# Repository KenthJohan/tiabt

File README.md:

# tiabt
Low cost 8 channels transimpedance amplifier with bluetooth.

## circuit1
The `/circuit1` is low cost.
* op-amp `MCP6004` 0.5 EUR<br>

|Name                  |Category|  EUR|Footprint |   |   |   |   |   |   |
|----------------------|--------|-----|----------|---|---|---|---|---|---|
| [MCP6004][3]         | Op-Amp |0.5  |SOIC-14   |   |   |   |   |   |   |
| [MCP3564][4]         | ADC    |6    |          |   |   |   |   |   |   |
| [nRF52840 Dongle][1] | MCU    |     |          |   |   |   |   |   |   |
|                      |        |     |          |   |   |   |   |   |   |
|                      |        |     |          |   |   |   |   |   |   |
|                      |        |     |          |   |   |   |   |   |   |
|                      |        |     |          |   |   |   |   |   |   |
|                      |        |     |          |   |   |   |   |   |   |
|                      |        |     |          |   |   |   |   |   |   |
|                      |        |     |          |   |   |   |   |   |   |

## circuit2
The `/circuit2` is high cost.

|Name                  |Category|  EUR|Footprint|   |   |   |   |   |   |
|----------------------|--------|-----|---------|---|---|---|---|---|---|
| [MCP6034][9]         | Op-Amp |0.5  |SOIC-14  |   |   |   |   |   |   |
| [MCP3564][4]         | ADC    |6    |         |   |   |   |   |   |   |
| [nRF52840 Dongle][1] | MCU    |     |         |   |   |   |   |   |   |
| [MAX6070][5]         | VREF   |     |SOT-23-6 |   |   |   |   |   |   |
| [LP2985-3.6][6]      | VREG   |     |SOT-23-5 |   |   |   |   |   |   |
| [LP5907MFX-4.5][7]   | VREG   |     |SOT-23-5 |   |   |   |   |   |   |
| [LM1117-5.0][8]      | VREG   |     |SOT-223-3|   |   |   |   |   |   |
|                      |        |     |         |   |   |   |   |   |   |
|                      |        |     |         |   |   |   |   |   |   |
|                      |        |     |         |   |   |   |   |   |   |
|                      |        |     |         |   |   |   |   |   |   |

[1]:https://www.nordicsemi.com/Products/Development-hardware/nrf52840-dongle
[2]:https://docs.zephyrproject.org/2.6.0/boards/arm/nrf52840dongle_nrf52840/doc/index.html
[3]:https://www.microchip.com/en-us/product/MCP6004
[4]:https://www.microchip.com/en-us/product/MCP3564
[5]:https://www.maximintegrated.com/en/products/analog/voltage-references/MAX6070.html
[6]:https://www.ti.com/product/LP2985
[7]:https://www.ti.com/product/LP5907
[8]:https://www.onsemi.com/products/power-management/linear-regulators-ldo/lm1117
[9]:https://www.microchip.com/en-us/product/MCP3564

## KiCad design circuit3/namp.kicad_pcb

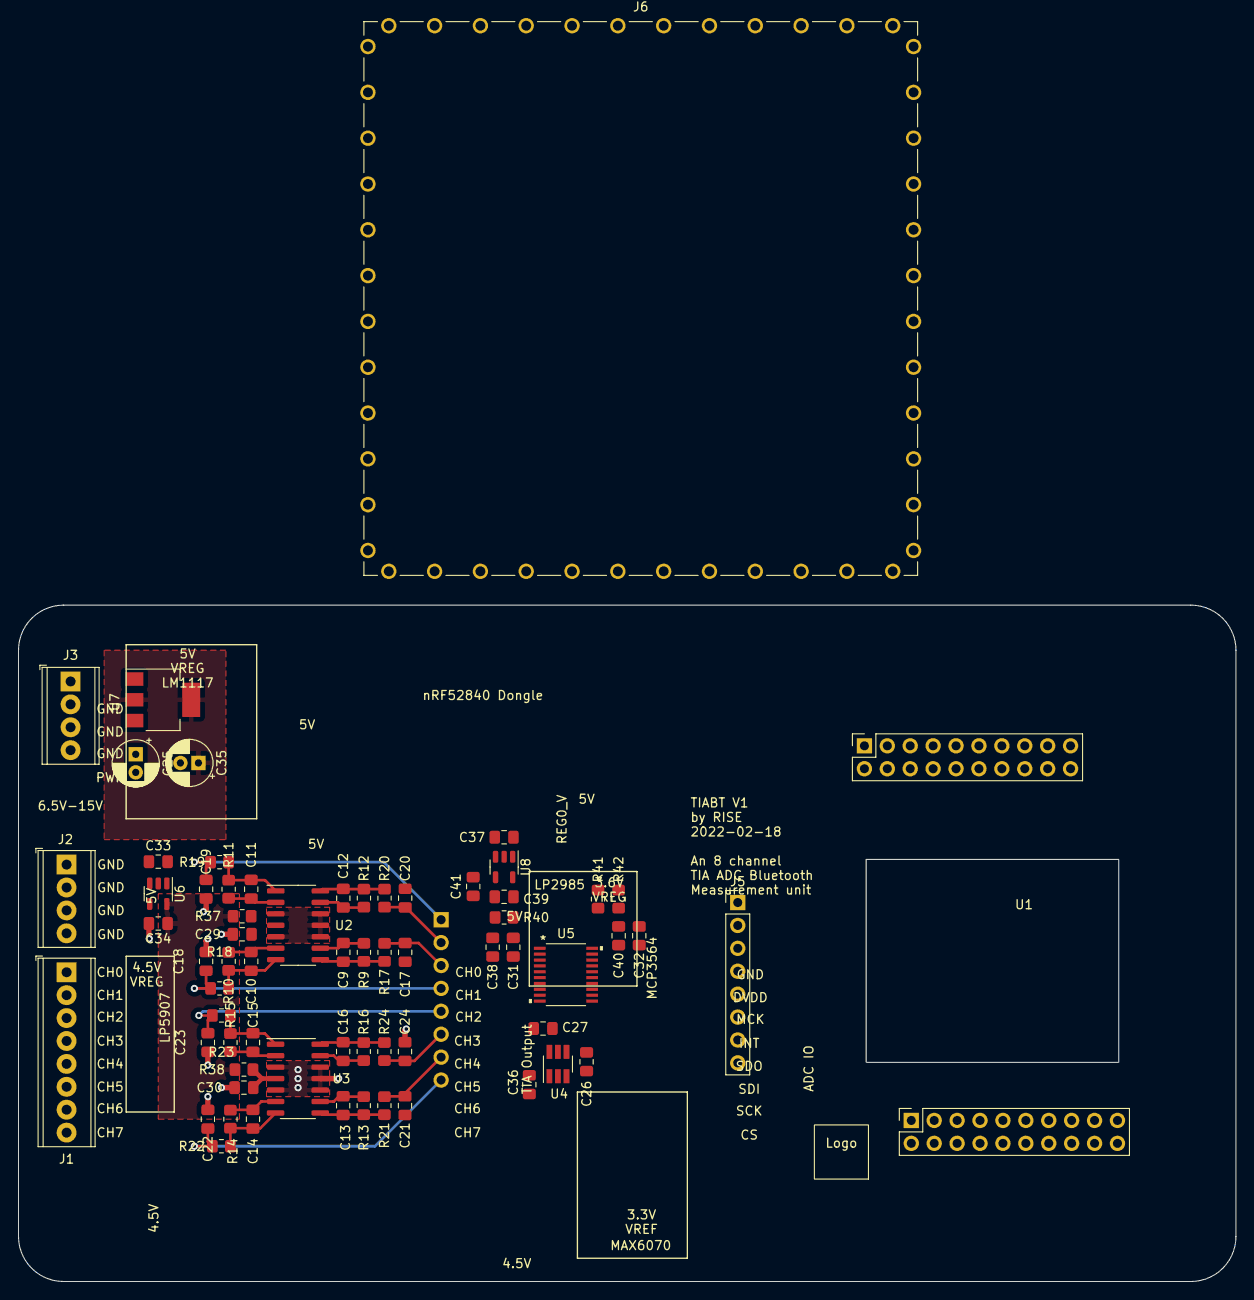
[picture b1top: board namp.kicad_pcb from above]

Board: 2 copper layers, 135.0 x 75.0 mm, 67 parts (1 on the bottom side), 42 nets.

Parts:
C9, C10, C11, C12, C13, C14, C15, C16: 10pF; C_0805_2012Metric_Pad1.18x1.45mm_HandSolder
C17, C18, C19, C20, C21, C22, C23, C24, C29, C30: C; C_0805_2012Metric_Pad1.18x1.45mm_HandSolder
C25, C35: C_Polarized; CP_Radial_D5.0mm_P2.00mm
C26, C27, C31, C32, C36, C38: 0.1µF; C_0805_2012Metric_Pad1.18x1.45mm_HandSolder
C33, C34, C37: 1uF; C_0805_2012Metric_Pad1.18x1.45mm_HandSolder
C39: 2.2uF; C_0805_2012Metric_Pad1.18x1.45mm_HandSolder
C40: 0.1uF; C_0805_2012Metric_Pad1.18x1.45mm_HandSolder
C41: 10nF; C_0805_2012Metric_Pad1.18x1.45mm_HandSolder
J1: Screw_Terminal_01x08; TerminalBlock_Phoenix_MPT-0,5-8-2.54_1x08_P2.54mm_Horizontal
J2, J3: Screw_Terminal_01x04; TerminalBlock_Phoenix_MPT-0,5-4-2.54_1x04_P2.54mm_Horizontal
J4: Conn_01x08_Female; PinHeader_1x08_P2.54mm_Vertical
J5: Conn_01x08_Male; PinHeader_1x08_P2.54mm_Vertical
J6: RFShield_OnePiece; Wuerth_36503605_60x60mm
R9, R10, R11, R12, R13, R14, R15, R16: 1M; R_0805_2012Metric_Pad1.20x1.40mm_HandSolder
R17, R18, R19, R20, R21, R22, R23, R24: 3k; R_0805_2012Metric_Pad1.20x1.40mm_HandSolder
R37, R38, R40, R42: 10; R_0805_2012Metric_Pad1.20x1.40mm_HandSolder
R41: 10k; R_0805_2012Metric_Pad1.20x1.40mm_HandSolder
U1: Sensor_OPDOLED
U2, U3: MCP6034; SOIC-14_3.9x8.7mm_P1.27mm
U4: MAX6070; SOT-23-6_Handsoldering
U5: MCP3564
U6: LP5907MFX-4.5; SOT-23-5
U7: LM1117-5.0; SOT-223-3_TabPin2
U8: LP2985-3.6; SOT-23-5

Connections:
+5V: C33.1, C35.1, C37.1, U6.1 (IN), U6.3 (EN), U7.2 (VO), U8.1 (VIN), U8.3 (ON/~OFF)
/ADC_CH0: C19.1, J4.1, R19.1, U5.5 (CH0)
/ADC_CH1: C20.1, J4.2, R20.1, U5.6 (CH1)
/ADC_CH2: C17.1, J4.3, R17.1, U5.7 (CH2)
/ADC_CH3: C18.1, J4.4, R18.1, U5.8 (CH3)
/ADC_CH4: C23.1, J4.5, R23.1, U5.9 (CH4)
/ADC_CH5: C24.1, J4.6, R24.1, U5.10 (CH5)
/ADC_CH6: C21.1, J4.7, R21.1, U5.11 (CH6)
/ADC_CH7: C22.1, J4.8, R22.1, U5.12 (CH7)
/CH0: C11.1, J1.1, R11.1, U1.1 (OPD0-), U2.2 (-)
/CH1: C12.1, J1.2, R12.1, U2.13 (-)
/CH2: C9.1, J1.3, R9.1, U2.9 (-)
/CH3: C10.1, J1.4, R10.1, U2.6 (-)
/CH4: C15.1, J1.5, R15.1, U3.2 (-)
/CH5: C16.1, J1.6, R16.1, U3.13 (-)
/CH6: C13.1, J1.7, R13.1, U3.9 (-)
/CH7: C14.1, J1.8, R14.1, U3.6 (-)
ADC_AVDD: C31.1, C38.1, R40.1, U5.1 (AVDD)
ADC_CS: J5.8, U5.13 (*CS)
ADC_DVDD: C32.1, C40.1, J5.2, R41.1, R42.1, U5.20 (DVDD)
ADC_INT: J5.4, R41.2, U5.17 (*IRQ/MDAT)
ADC_MCK: J5.3, U5.18 (MCLKIN)
ADC_SCK: J5.7, U5.14 (SCK)
ADC_SDI: J5.6, U5.15 (SDI)
ADC_SDO: J5.5, U5.16 (SDO)
ADC_VREF+: C27.1, U4.5 (OUTS), U4.6 (OUTF), U5.4 (REFIN+)
GND: C17.2, C18.2, C19.2, C20.2, C21.2, C22.2, C23.2, C24.2, C25.2, C26.2, C27.2, C29.2, C30.2, C31.2, C32.2, C33.2, C34.2, C35.2, C36.2, C37.2, C38.2, C39.2, C40.2, C41.2, J2.1, J2.2, J2.3, J2.4, J3.1, J3.2, J3.3, J5.1, J6.1 (Shield), U2.3 (+), U2.5 (+), U2.10 (+), U2.11 (V-), U2.12 (+), U3.3 (+), U3.5 (+), U3.10 (+), U3.11 (V-), U3.12 (+), U4.2 (GND), U5.2 (AGND), U5.3 (REFIN-), U5.19 (DGND), U6.2 (GND), U7.1 (GND), U8.2 (GND)
unnamed: C9.2, R9.2, R17.2, U2.8
unnamed: C10.2, R10.2, R18.2, U2.7
unnamed: C11.2, R11.2, R19.2, U2.1
unnamed: C12.2, R12.2, R20.2, U2.14
unnamed: C13.2, R13.2, R21.2, U3.8
unnamed: C14.2, R14.2, R22.2, U3.7
unnamed: C15.2, R15.2, R23.2, U3.1
unnamed: C16.2, R16.2, R24.2, U3.14
unnamed: C36.1, U4.1 (FILTER)
unnamed: C39.1, R40.2, U8.5 (VOUT)
unnamed: C41.1, U8.4 (BP)
PWR_MAX15V: C25.1, J3.4, U7.3 (VI)
TIA0_V: C29.1, R37.2, U2.4 (V+)
TIA1_V: C30.1, R38.2, U3.4 (V+)
TIA_4.5V: C26.1, C34.1, R37.1, R38.1, U4.3 (EN), U4.4 (IN), U6.5 (OUT)

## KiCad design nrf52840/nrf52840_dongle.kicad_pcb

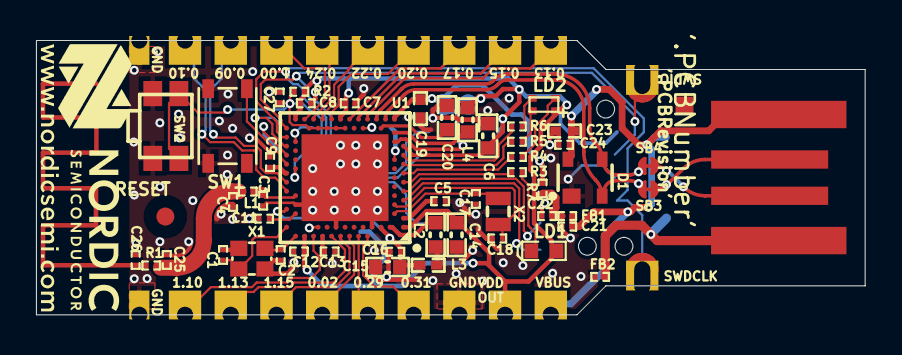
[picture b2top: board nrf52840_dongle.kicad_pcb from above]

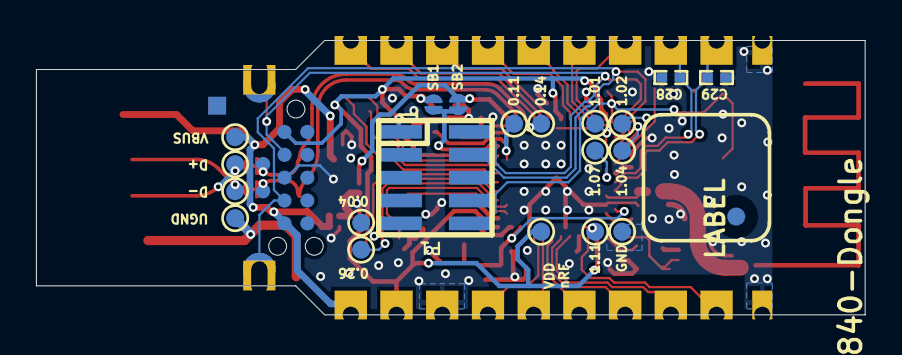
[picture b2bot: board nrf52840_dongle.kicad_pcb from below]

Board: 2 copper layers, 46.0 x 15.2 mm, 97 parts (23 on the bottom side), 64 nets.

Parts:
0.02, 0.09, 0.10, 0.13, 0.15, 0.17, 0.20, 0.22, 0.24, 0.29, 0.31, 1.00, 1.10, 1.13, 1.15: CH; _Applications_test_rsk_lib_RSK-ONLY_PcbLib_Castellated_Hole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
0.04, 0.26, 1.01, 1.02, 1.04, 1.07: Ø1.0mm,SMD; _Applications_test_rsk_lib_RSK-ONLY_PcbLib_Passive.PcbLib_T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
0.11, 0.14, 1.11: Ø1.0mm,SMD; _Applications_test_rsk_lib_RSK-ONLY_Nordic Passive DB.DbLib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
C1, C2, C17, C18: 12pF; _Applications_test_rsk_lib_RSK-ONLY_PcbLib_Passive.PcbLib_C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
C3: 0.8pF; _Applications_test_rsk_lib_RSK-ONLY_PcbLib_Passive.PcbLib_C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
C4: 0.5pF; _Applications_test_rsk_lib_RSK-ONLY_PcbLib_Passive.PcbLib_C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
C5, C7, C8, C12, C22, C24, C27: 100nF; _Applications_test_rsk_lib_RSK-ONLY_PcbLib_Passive.PcbLib_C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
C6, C20: 4.7µF; _Applications_test_rsk_lib_RSK-ONLY_Nordic Passive DB.DbLib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
C9: 820pF; _Applications_test_rsk_lib_RSK-ONLY_PcbLib_Passive.PcbLib_C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
C11: 100pF; _Applications_test_rsk_lib_RSK-ONLY_PcbLib_Passive.PcbLib_C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
C13, C25, C28, C29: N.C.; _Applications_test_rsk_lib_RSK-ONLY_PcbLib_Passive.PcbLib_C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
C14, C15: 1.0µF; _Applications_test_rsk_lib_RSK-ONLY_Nordic Passive DB.DbLib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
C16: 47nF; _Applications_test_rsk_lib_RSK-ONLY_PcbLib_Passive.PcbLib_C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
C19, C23: 4.7µF; _Applications_test_rsk_lib_RSK-ONLY_PcbLib_Passive.PcbLib_C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
C21: 10nF; _Applications_test_rsk_lib_RSK-ONLY_PcbLib_Passive.PcbLib_C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
C26: 1.5pF; _Applications_test_rsk_lib_RSK-ONLY_Nordic Passive DB.DbLib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
D1: PRTR5V0U2X; _Applications_test_rsk_lib_RSK-ONLY_PcbLib_pcblib.PcbLib_SO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
D+: Ø1.0mm,SMD; _Applications_test_rsk_lib_RSK-ONLY_PcbLib_Passive.PcbLib_T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
D-: Ø1.0mm,SMD; _Applications_test_rsk_lib_RSK-ONLY_PcbLib_Passive.PcbLib_T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
DN: Ø1.0mm,SMD; _Applications_hardware_pca10059_trunk_altium_files_pca10059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
DP: Ø1.0mm,SMD; _Applications_hardware_pca10059_trunk_altium_files_pca10059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
FB1, FB2: 120R/0.85A; _Applications_test_rsk_lib_RSK-ONLY_PcbLib_Passive.PcbLib_I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
Fid1: Fiducial mark; _Applications_test_rsk_lib_RSK-ONLY_Nordic Passive DB.DbLib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
Fid2: Fiducial mark; _Applications_test_rsk_lib_RSK-ONLY_PcbLib_Passive.PcbLib_F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
GND1: GND; _Applications_test_rsk_lib_RSK-ONLY_PcbLib_Castellated_Hole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
GND2, GND3: GND; _Applications_test_rsk_lib_RSK-ONLY_Nordic Passive DB.DbLib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
GND4: GND; _Applications_test_rsk_lib_RSK-ONLY_PcbLib_Passive.PcbLib_T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
J1: USB-A; _Repositories_Applications_test_rsk_lib_RSK-ONLY_PcbLib_PAS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
J2: TC2050-IDC; TC2050-IDC-NLFP
L1: 4.7nH; _Applications_test_rsk_lib_RSK-ONLY_PcbLib_Passive.PcbLib_I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
L2: 10µH; INDC1608X06L
L3: 15nH; INDC1005X04L
L4: 10µH; _Applications_test_rsk_lib_RSK-ONLY_PcbLib_Passive.PcbLib_I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
LD1: L0603G; _Applications_test_rsk_lib_RSK-ONLY_Nordic Discrete DB.DbLi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
LD2: LED RGB; _Applications_test_rsk_lib_RSK-ONLY_Nordic Discrete DB.DbLi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
P1: Pin Header 2x5, 1.27mm; _Applications_test_rsk_lib_RSK-ONLY_Nordic Passive DB.DbLib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
R1: 0R; _Applications_test_rsk_lib_RSK-ONLY_PcbLib_Passive.PcbLib_R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
R2: 10k; _Applications_test_rsk_lib_RSK-ONLY_PcbLib_Passive.PcbLib_R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
R3: 220R; _Applications_test_rsk_lib_RSK-ONLY_PcbLib_Passive.PcbLib_R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
R4: 1k2; _Applications_test_rsk_lib_RSK-ONLY_PcbLib_Passive.PcbLib_R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
R5: 2k2; _Applications_test_rsk_lib_RSK-ONLY_PcbLib_Passive.PcbLib_R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
R6: 390R; _Applications_test_rsk_lib_RSK-ONLY_PcbLib_Passive.PcbLib_R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
R7: 4R7; _Applications_test_rsk_lib_RSK-ONLY_PcbLib_Passive.PcbLib_R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
SB1, SB2, SB3, SB4: Solderbridge; _Applications_test_rsk_lib_RSK-ONLY_PcbLib_Passive.PcbLib_S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
SW1: PB SW; _Applications_test_rsk_lib_RSK-ONLY_Nordic Discrete DB.DbLi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
SW2: PTS840 GK SMTR LFS; _Applications_test_rsk_lib_RSK-ONLY_Nordic Discrete DB.DbLi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
SWDCLK: CH; _Applications_test_rsk_lib_RSK-ONLY_Nordic Passive DB.DbLib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
SWDIO: CH; _Applications_test_rsk_lib_RSK-ONLY_Nordic Passive DB.DbLib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
U1: nRF52840-QIAA; _Applications_test_rsk_lib_RSK-ONLY_PcbLib_AQFN50P700X700X8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
UGND: Ø1.0mm,SMD; _Applications_test_rsk_lib_RSK-ONLY_PcbLib_Passive.PcbLib_T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
VBUS1: VBUS; _Applications_test_rsk_lib_RSK-ONLY_PcbLib_Castellated_Hole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
VBUS2: VBUS; _Applications_test_rsk_lib_RSK-ONLY_PcbLib_Passive.PcbLib_T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
VDD OUT: CH; _Applications_test_rsk_lib_RSK-ONLY_PcbLib_Castellated_Hole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
VDD nRF: Ø1.0mm,SMD; _Applications_test_rsk_lib_RSK-ONLY_PcbLib_Passive.PcbLib_T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
X1: 32MHz; _Applications_test_rsk_lib_RSK-ONLY_Nordic Discrete DB.DbLi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
X2: 32.768kHz; _Applications_test_rsk_lib_RSK-ONLY_PcbLib_pcblib.PcbLib_XT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

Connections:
ANT: C26.2, R1.2
DEC1: C5.1, U1.C1
DEC3: C11.1, U1.D23
DEC4_6: C15.2, C16.1, L3.1, U1.B5, U1.E24
D_N: D1.2, DN.1, SB3.1, U1.AD4
D_P: D1.3, DP.1, SB4.1, U1.AD6
GND: C2.2, C3.1, C4.1, C5.2, C6.2, C7.2, C8.2, C9.2, C11.2, C12.2, C13.2, C14.2, C15.1, C16.2, C17.2, C18.2, C19.2, C20.2, C21.1, C22.1, C23.1, C24.1, C25.2, C26.1, C27.1, C28.1, C29.2, D1.1, FB2.2, GND1.1, GND2.1, GND3.1, GND4.1, J2.3, P1.3, P1.5, P1.9, SW1.2, SW2.2, U1.74, U1.B7, U1.B15, U1.F23, X1.2
LED1: R3.1, U1.L1
LED2_B: R6.1, U1.U1
LED2_G: R5.1, U1.R1
LED2_R: R4.1, U1.N1
NetC1_2: C1.2, X1.4
NetC3_2: C3.2, L1.1, U1.H23
NetC9_1: C9.1, U1.N24
NetC13_1: C13.1, U1.A18
NetC20_1: C20.1, U1.AC5
NetD+_1: D+.1, J1.3, SB4.2
NetD-_1: D-.1, J1.2, SB3.2
NetFB2_1: FB2.1, J1.4, UGND.1
NetL2_1: L2.1, L3.2
NetL2_2: L2.2, U1.B3
NetL4_2: L4.2, U1.AB2
NetLD1_1: LD1.1, R3.2
NetLD2_1: LD2.1, R4.2
NetLD2_2: LD2.2, R5.2
NetLD2_3: LD2.3, R6.2
NetSB1_2: SB1.2, SB2.1, U1.Y2
P0.00/XL1: C17.1, U1.D2, X2.1
P0.01/XL2: C18.1, U1.F2, X2.2
P0.02: 0.02.1, U1.A12
P0.04: 0.04.1, U1.J1
P0.09: 0.09.1, C28.2, U1.L24
P0.10: 0.10.1, C29.1, U1.J24
P0.11: 0.11.1, U1.T2
P0.13: 0.13.1, U1.AD8
P0.14: 0.14.1, U1.AC9
P0.15: 0.15.1, U1.AD10
P0.17: 0.17.1, U1.AD12
P0.20: 0.20.1, U1.AD16
P0.22: 0.22.1, U1.AD18
P0.24: 0.24.1, U1.AD20
P0.26: 0.26.1, U1.G1
P0.29: 0.29.1, U1.A10
P0.31: 0.31.1, U1.A8
P1.00: 1.00.1, U1.AD22
P1.01: 1.01.1, U1.Y23
P1.02: 1.02.1, U1.W24
P1.04: 1.04.1, U1.U24
P1.07: 1.07.1, U1.P23
P1.10: 1.10.1, U1.A20
P1.11: 1.11.1, U1.B19
P1.13: 1.13.1, U1.A16
P1.15: 1.15.1, U1.A14
RESET: C27.2, P1.10, R2.1, SW2.1, U1.AC13, U1.AC15, U1.AC17, U1.AC19, U1.AC21
RF: C4.2, C25.1, L1.2, R1.1
SW1: SW1.1, U1.R24
SWDCLK: J2.4, P1.4, SWDCLK.1, U1.AA24
SWDIO: J2.2, P1.2, SWDIO.1, U1.AC24
VBUS: C22.2, FB1.2, R7.2
VBUS': C21.2, C23.2, C24.2, D1.4, FB1.1, J1.1, J2.5, VBUS1.1, VBUS2.1
VBUS_nRF: C19.1, R7.1, SB2.2, U1.AD2
VDD_nRF: C6.1, C7.1, C8.1, C12.1, C14.1, J2.1, L4.1, LD1.2, LD2.4, P1.1, R2.2, SB1.1, U1.A22, U1.AD14, U1.AD23, U1.B1, U1.W1, VDD OUT.1, VDD nRF.1
XC1: C1.1, U1.B24, X1.1
XC2: C2.1, U1.A23, X1.3

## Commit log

2022-01-17 init
2022-01-18 test
2022-02-11 Changed to 0805
2022-02-14 added holes
2022-03-07 added code example
2022-04-01 Reading correct voltage from 1.5V battery.
2022-04-04 scanmode
2022-04-05 calculate correct voltage
2022-04-29 Remove adc temporary
2022-06-13 addded circuit 3
2022-06-16 added moloko sensor

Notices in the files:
parts and their libraries:
Copyright 2021 Accelerated Designs. All rights reserved.
